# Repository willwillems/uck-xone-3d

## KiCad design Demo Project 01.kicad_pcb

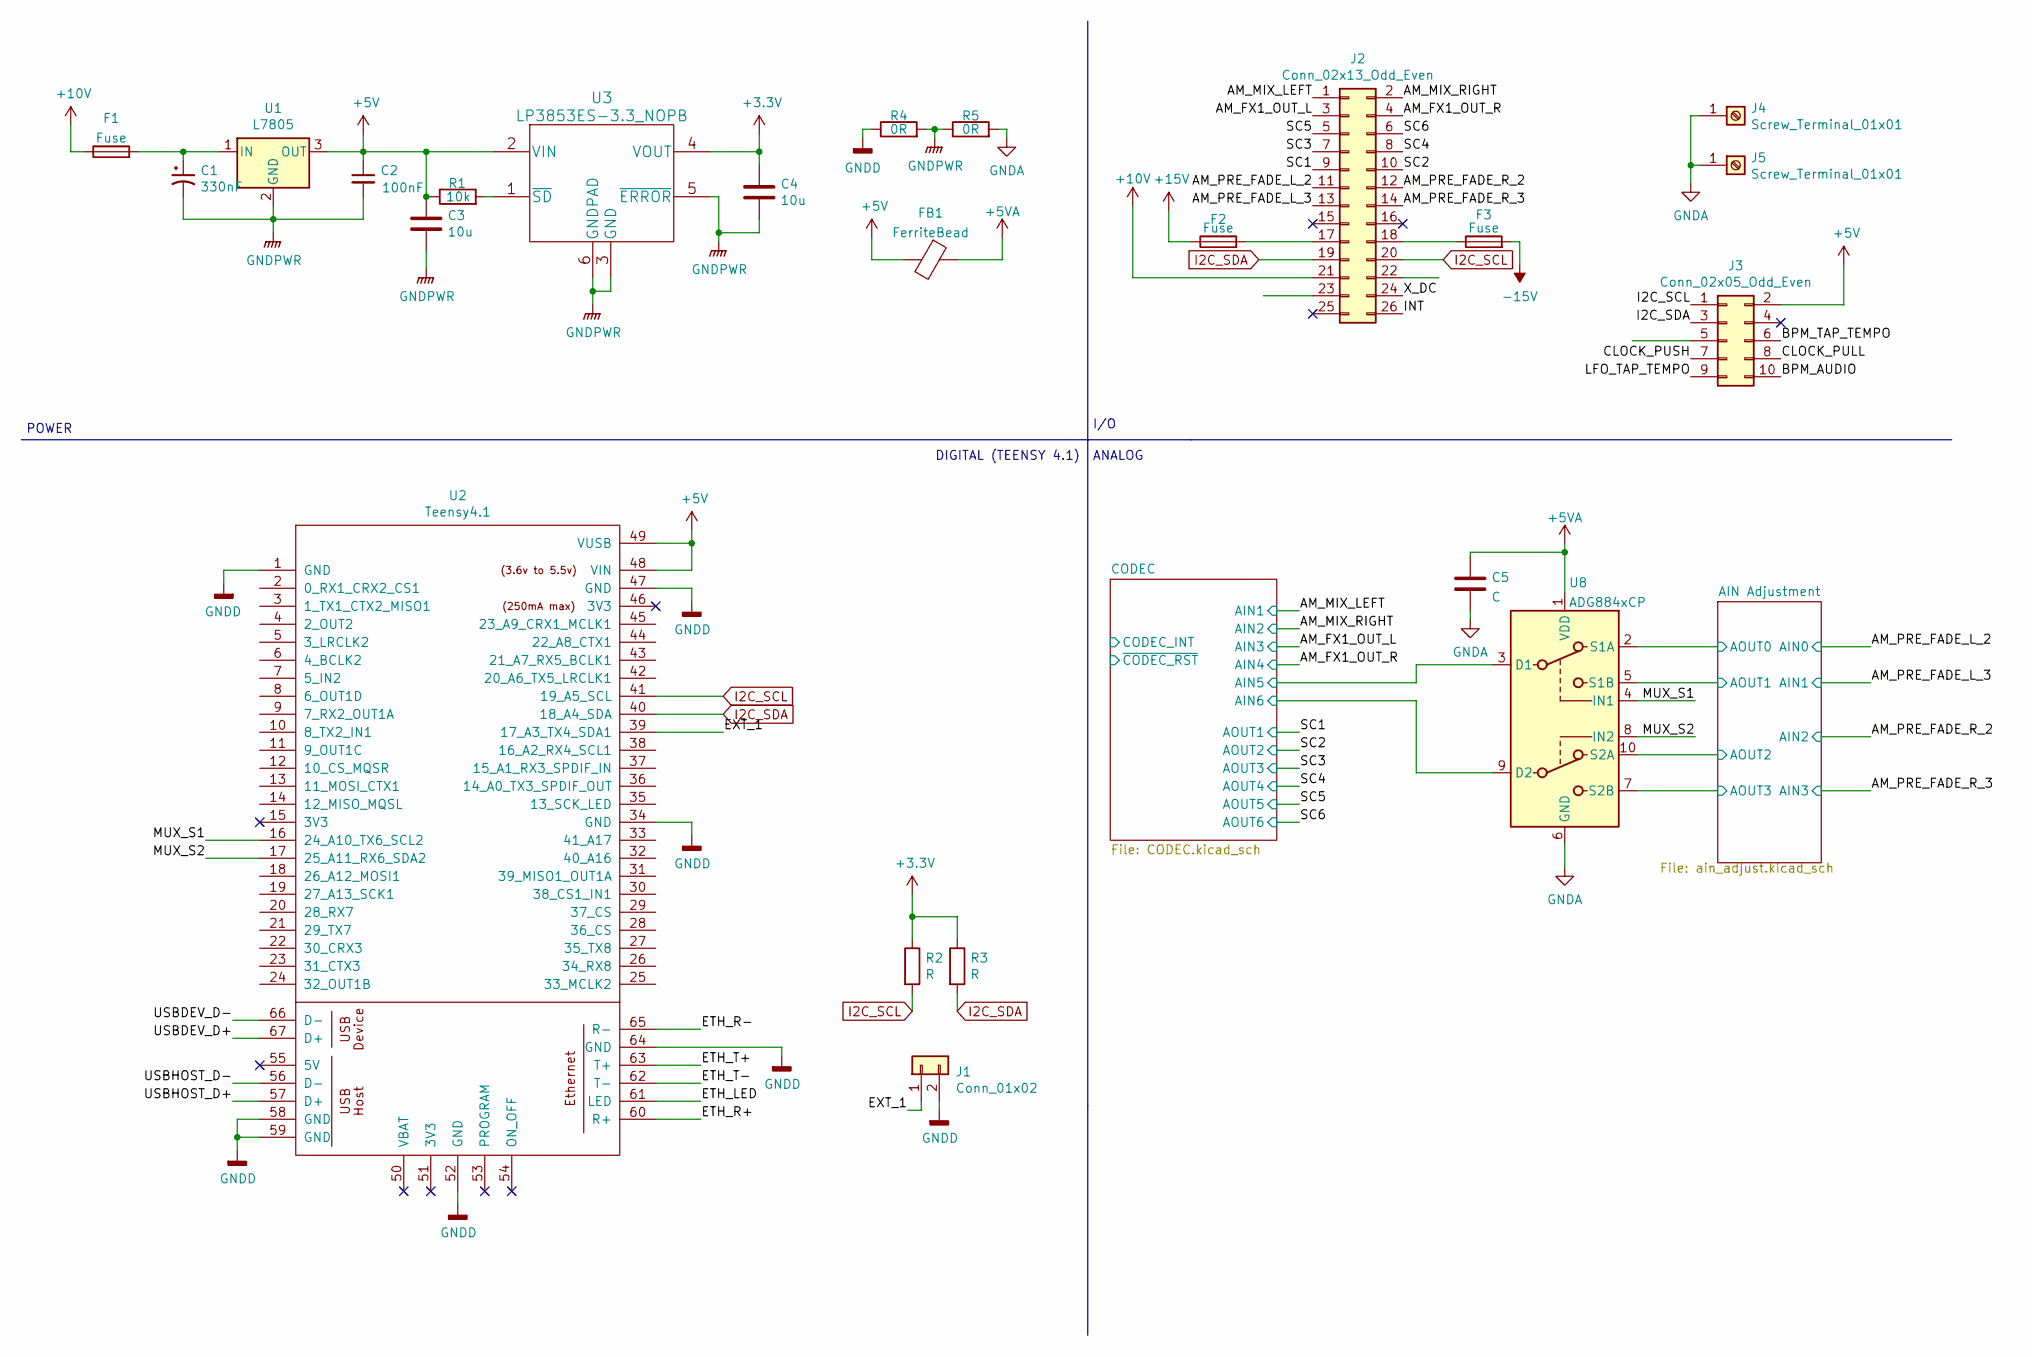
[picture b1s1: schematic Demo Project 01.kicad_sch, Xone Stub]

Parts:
C1: 330nF; CP_Radial_D10.0mm_P5.00mm
C2: 100nF; C_0603_1608Metric
C3, C4: 10u; C_0603_1608Metric_Pad1.08x0.95mm_HandSolder
C5: C; C_0603_1608Metric_Pad1.08x0.95mm_HandSolder
F1, F2, F3: Fuse; Fuse_0805_2012Metric
FB1: FerriteBead; C_0805_2012Metric_Pad1.18x1.45mm_HandSolder
J1: Conn_01x02; PinHeader_1x02_P2.54mm_Vertical
J2: Conn_02x13_Odd_Even; PinHeader_2x13_P2.54mm_Vertical
J3: Conn_02x05_Odd_Even; IDC-Header_2x05_P2.54mm_Horizontal
J4, J5: Screw_Terminal_01x01; MountingHole_3.2mm_M3_Pad_Via
R1: 10k; R_0603_1608Metric_Pad0.98x0.95mm_HandSolder
R2, R3: R; R_0603_1608Metric_Pad0.98x0.95mm_HandSolder
R4, R5: 0R; R_0603_1608Metric_Pad0.98x0.95mm_HandSolder
U1: L7805; TO-263-2
U2: Teensy4.1; Teensy41
U3: LP3853ES-3.3_NOPB; TO-263-5_TabPin6
U8: ADG884xCP; LFCSP-WD-10-1EP_3x3mm_P0.5mm_EP1.64x2.38mm

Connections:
+3V3: C4.1, R2.1, R3.1, U3.4 (VOUT); also elsewhere on the board
+5V: C2.1, C3.1, FB1.2, J3.2, R1.1, U1.3 (OUT), U2.48 (VIN), U2.49 (VUSB), U3.2 (VIN)
+5VA: C5.1, FB1.1, U8.1 (VDD); also elsewhere on the board
+10V: F1.1, J2.21
+15V: F2.1; also elsewhere on the board
-15V: F3.2; also elsewhere on the board
/AIN Adjustment/AOUT0: U8.2 (S1A); also elsewhere on the board
/AIN Adjustment/AOUT1: U8.5 (S1B); also elsewhere on the board
/AIN Adjustment/AOUT2: U8.10 (S2A); also elsewhere on the board
/AIN Adjustment/AOUT3: U8.7 (S2B); also elsewhere on the board
/AM_FX1_OUT_L: J2.3; also elsewhere on the board
/AM_FX1_OUT_R: J2.4; also elsewhere on the board
/AM_MIX_LEFT: J2.1; also elsewhere on the board
/AM_MIX_RIGHT: J2.2; also elsewhere on the board
/AM_PRE_FADE_L_2: J2.11; also elsewhere on the board
/AM_PRE_FADE_L_3: J2.13; also elsewhere on the board
/AM_PRE_FADE_R_2: J2.12; also elsewhere on the board
/AM_PRE_FADE_R_3: J2.14; also elsewhere on the board
/BPM_AUDIO: J3.10
/BPM_TAP_TEMPO: J3.6
/CLOCK_PULL: J3.8
/CLOCK_PUSH: J3.7
/CODEC/AIN5: U8.3 (D1); also elsewhere on the board
/CODEC/AIN6: U8.9 (D2); also elsewhere on the board
/ETH_LED: U2.61 (LED)
/ETH_R+: U2.60 (R+)
/ETH_R-: U2.65 (R-)
/ETH_T+: U2.63 (T+)
/ETH_T-: U2.62 (T-)
/EXT_1: J1.1, U2.39 (17_A3_TX4_SDA1)
/INT: J2.26
/LFO_TAP_TEMPO: J3.9
/MUX_S1: U2.16 (24_A10_TX6_SCL2), U8.4 (IN1)
/MUX_S2: U2.17 (25_A11_RX6_SDA2), U8.8 (IN2)
/SC1: J2.9; also elsewhere on the board
/SC2: J2.10; also elsewhere on the board
/SC3: J2.7; also elsewhere on the board
/SC4: J2.8; also elsewhere on the board
/SC5: J2.5; also elsewhere on the board
/SC6: J2.6; also elsewhere on the board
/USBDEV_D+: U2.67 (D+)
/USBDEV_D-: U2.66 (D-)
/USBHOST_D+: U2.57 (D+)
/USBHOST_D-: U2.56 (D-)
/X_DC: J2.24
GNDA: C5.2, J4.1, J5.1, R5.2, U8.6 (GND), U8.11 (GND); also elsewhere on the board
GNDD: J1.2, R4.1, U2.1 (GND), U2.34 (GND), U2.47 (GND), U2.52 (GND), U2.58 (GND), U2.59 (GND), U2.64 (GND); also elsewhere on the board
GNDPWR: C1.2, C2.2, C3.2, C4.2, R4.2, R5.1, U1.2 (GND), U3.3 (GND), U3.5 (~ERROR), U3.6 (GNDPAD)
I2C_SCL: J2.20, J3.1, R2.2, U2.41 (19_A5_SCL); also elsewhere on the board
I2C_SDA: J2.19, J3.3, R3.2, U2.40 (18_A4_SDA); also elsewhere on the board
unnamed: C1.1, F1.2, U1.1 (IN)
unnamed: F2.2, J2.17
unnamed: F3.1, J2.18
unnamed: R1.2, U3.1 (~SD)

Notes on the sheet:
I/O
ANALOG
DIGITAL (TEENSY 4.1)
POWER

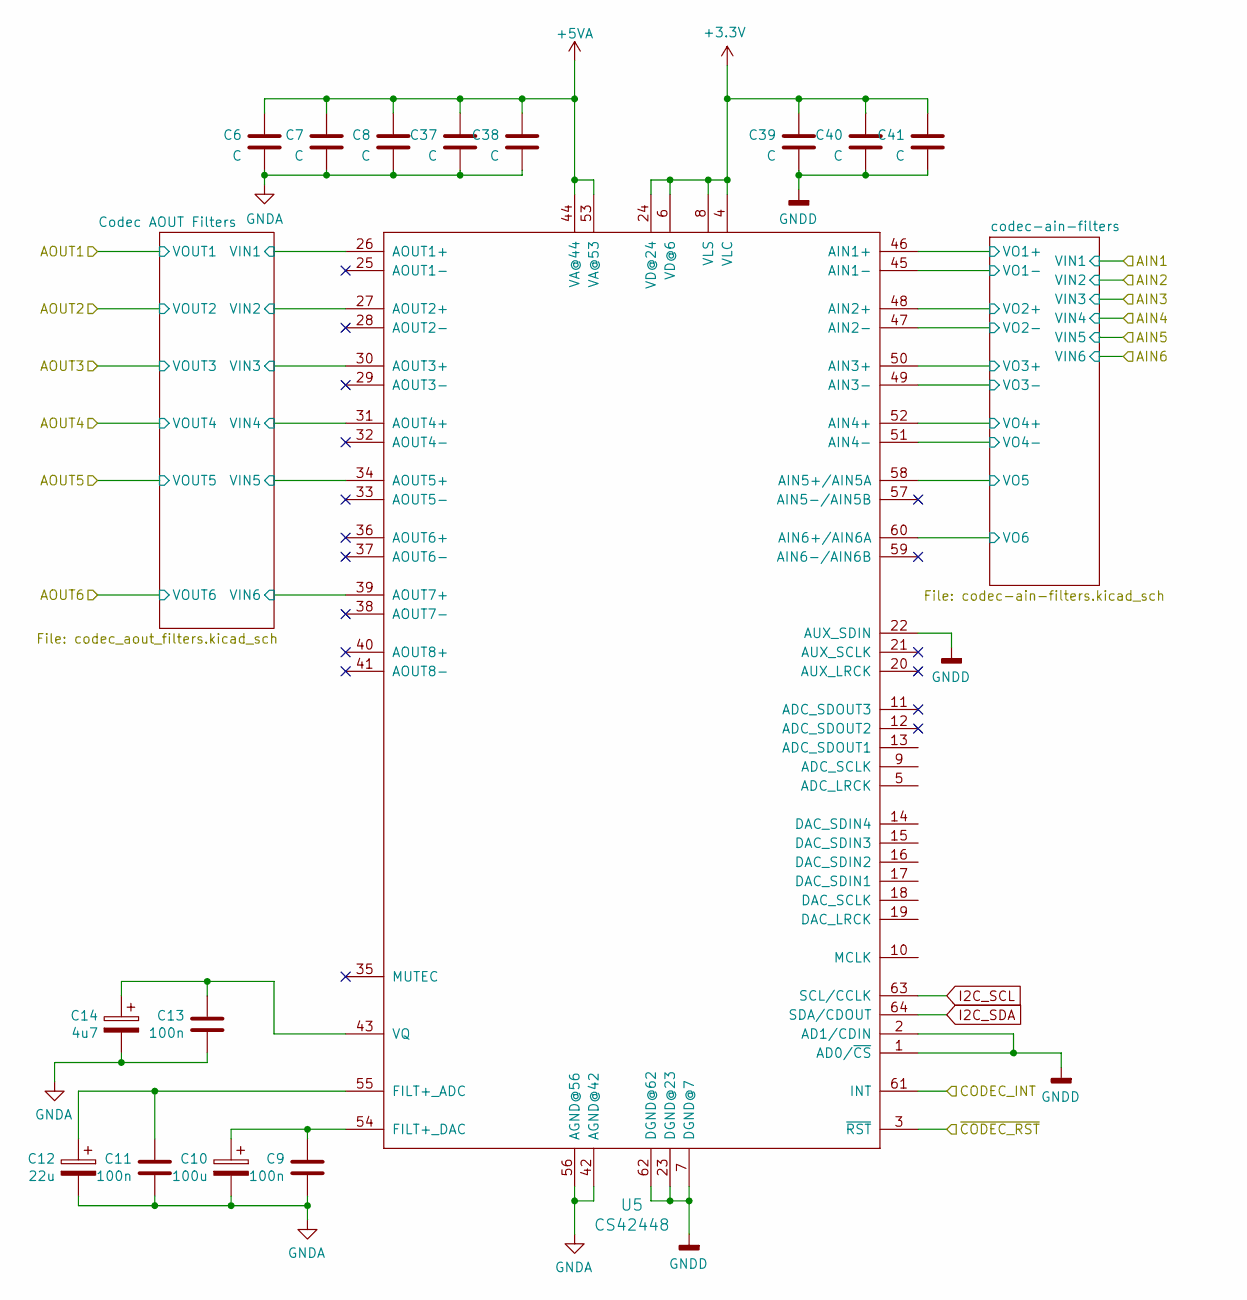
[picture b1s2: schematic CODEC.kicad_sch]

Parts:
C6, C7, C8, C37, C38, C39, C40, C41: C; C_0603_1608Metric_Pad1.08x0.95mm_HandSolder
C9, C11, C13: 100n; C_0603_1608Metric_Pad1.08x0.95mm_HandSolder
C10: 100u; C_0603_1608Metric_Pad1.08x0.95mm_HandSolder
C12: 22u; C_0603_1608Metric_Pad1.08x0.95mm_HandSolder
C14: 4u7; C_0603_1608Metric_Pad1.08x0.95mm_HandSolder
U5: CS42448; LQFP-64_10x10mm_P0.5mm

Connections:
+3V3: C39.1, C40.1, C41.1, U5.4 (VLC), U5.6 (VD@6), U5.8 (VLS), U5.24 (VD@24); also elsewhere on the board
+5VA: C6.1, C7.1, C8.1, C37.1, C38.1, U5.44 (VA@44), U5.53 (VA@53); also elsewhere on the board
/CODEC/CODEC_INT: U5.61 (INT)
/CODEC/Codec AOUT Filters/VIN1: U5.26 (AOUT1+); also elsewhere on the board
/CODEC/Codec AOUT Filters/VIN2: U5.27 (AOUT2+); also elsewhere on the board
/CODEC/Codec AOUT Filters/VIN3: U5.30 (AOUT3+); also elsewhere on the board
/CODEC/Codec AOUT Filters/VIN4: U5.31 (AOUT4+); also elsewhere on the board
/CODEC/Codec AOUT Filters/VIN5: U5.34 (AOUT5+); also elsewhere on the board
/CODEC/Codec AOUT Filters/VIN6: U5.39 (AOUT7+); also elsewhere on the board
/CODEC/codec-ain-filters/VO1+: U5.46 (AIN1+); also elsewhere on the board
/CODEC/codec-ain-filters/VO1-: U5.45 (AIN1-); also elsewhere on the board
/CODEC/codec-ain-filters/VO2+: U5.48 (AIN2+); also elsewhere on the board
/CODEC/codec-ain-filters/VO2-: U5.47 (AIN2-); also elsewhere on the board
/CODEC/codec-ain-filters/VO3+: U5.50 (AIN3+); also elsewhere on the board
/CODEC/codec-ain-filters/VO3-: U5.49 (AIN3-); also elsewhere on the board
/CODEC/codec-ain-filters/VO4+: U5.52 (AIN4+); also elsewhere on the board
/CODEC/codec-ain-filters/VO4-: U5.51 (AIN4-); also elsewhere on the board
/CODEC/codec-ain-filters/VO5: U5.58 (AIN5+/AIN5A); also elsewhere on the board
/CODEC/codec-ain-filters/VO6: U5.60 (AIN6+/AIN6A); also elsewhere on the board
/CODEC/~CODEC_RST: U5.3 (~RST)
GNDA: C6.2, C7.2, C8.2, C9.2, C10.2, C11.2, C12.2, C13.2, C14.2, C37.2, C38.2, U5.42 (AGND@42), U5.56 (AGND@56); also elsewhere on the board
GNDD: C39.2, C40.2, C41.2, U5.1 (AD0/~CS), U5.2 (AD1/CDIN), U5.7 (DGND@7), U5.22 (AUX_SDIN), U5.23 (DGND@23), U5.62 (DGND@62); also elsewhere on the board
I2C_SCL: U5.63 (SCL/CCLK); also elsewhere on the board
I2C_SDA: U5.64 (SDA/CDOUT); also elsewhere on the board
unnamed: C9.1, C10.1, U5.54 (FILT+_DAC)
unnamed: C11.1, C12.1, U5.55 (FILT+_ADC)
unnamed: C13.1, C14.1, U5.43 (VQ)

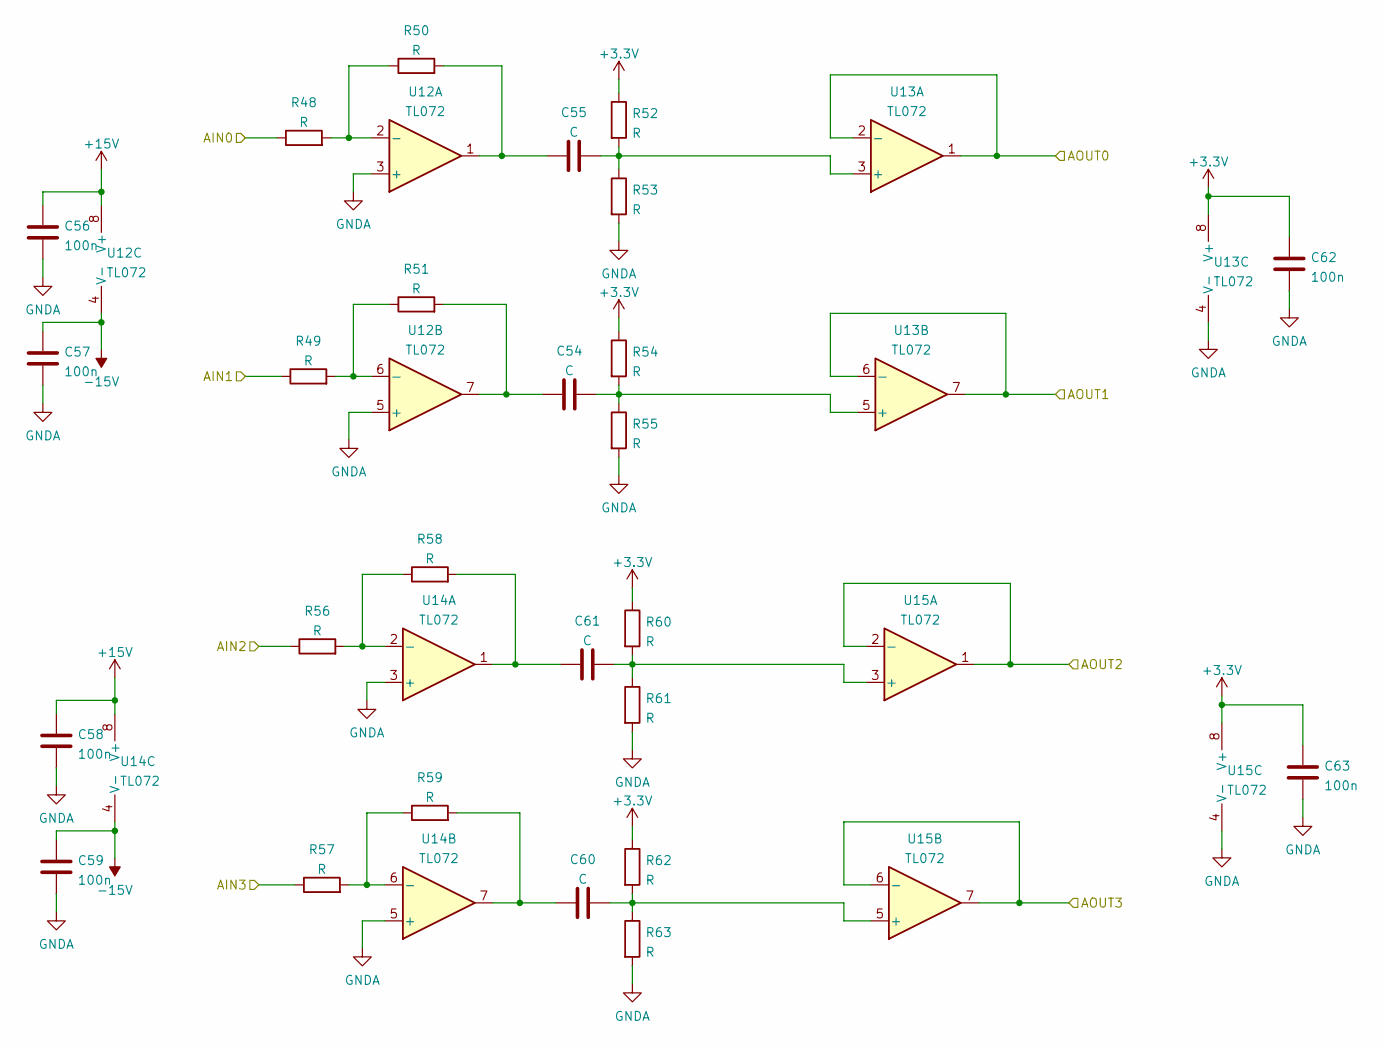
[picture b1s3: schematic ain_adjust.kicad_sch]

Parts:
C54, C55, C60, C61: C; C_0603_1608Metric_Pad1.08x0.95mm_HandSolder
C56, C57, C58, C59, C62, C63: 100n; C_0603_1608Metric_Pad1.08x0.95mm_HandSolder
R48, R49, R50, R51, R52, R53, R54, R55, R56, R57, R58, R59, R60, R61, R62, R63: R; R_0603_1608Metric_Pad0.98x0.95mm_HandSolder
U12, U13, U14, U15: TL072; SOIC-8_3.9x4.9mm_P1.27mm

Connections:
+3V3: C62.1, C63.1, R52.1, R54.1, R60.1, R62.1, U13.8 (V+), U15.8 (V+); also elsewhere on the board
+15V: C56.1, C58.1, U12.8 (V+), U14.8 (V+); also elsewhere on the board
-15V: C57.1, C59.1, U12.4 (V-), U14.4 (V-); also elsewhere on the board
/AIN Adjustment/AOUT0: U13.1, U13.2 (-); also elsewhere on the board
/AIN Adjustment/AOUT1: U13.6 (-), U13.7; also elsewhere on the board
/AIN Adjustment/AOUT2: U15.1, U15.2 (-); also elsewhere on the board
/AIN Adjustment/AOUT3: U15.6 (-), U15.7; also elsewhere on the board
/AM_PRE_FADE_L_2: R48.1; also elsewhere on the board
/AM_PRE_FADE_L_3: R49.1; also elsewhere on the board
/AM_PRE_FADE_R_2: R56.1; also elsewhere on the board
/AM_PRE_FADE_R_3: R57.1; also elsewhere on the board
GNDA: C56.2, C57.2, C58.2, C59.2, C62.2, C63.2, R53.2, R55.2, R61.2, R63.2, U12.3 (+), U12.5 (+), U13.4 (V-), U14.3 (+), U14.5 (+), U15.4 (V-); also elsewhere on the board
unnamed: C54.1, R51.2, U12.7
unnamed: C54.2, R54.2, R55.1, U13.5 (+)
unnamed: C55.1, R50.2, U12.1
unnamed: C55.2, R52.2, R53.1, U13.3 (+)
unnamed: C60.1, R59.2, U14.7
unnamed: C60.2, R62.2, R63.1, U15.5 (+)
unnamed: C61.1, R58.2, U14.1
unnamed: C61.2, R60.2, R61.1, U15.3 (+)
unnamed: R48.2, R50.1, U12.2 (-)
unnamed: R49.2, R51.1, U12.6 (-)
unnamed: R56.2, R58.1, U14.2 (-)
unnamed: R57.2, R59.1, U14.6 (-)

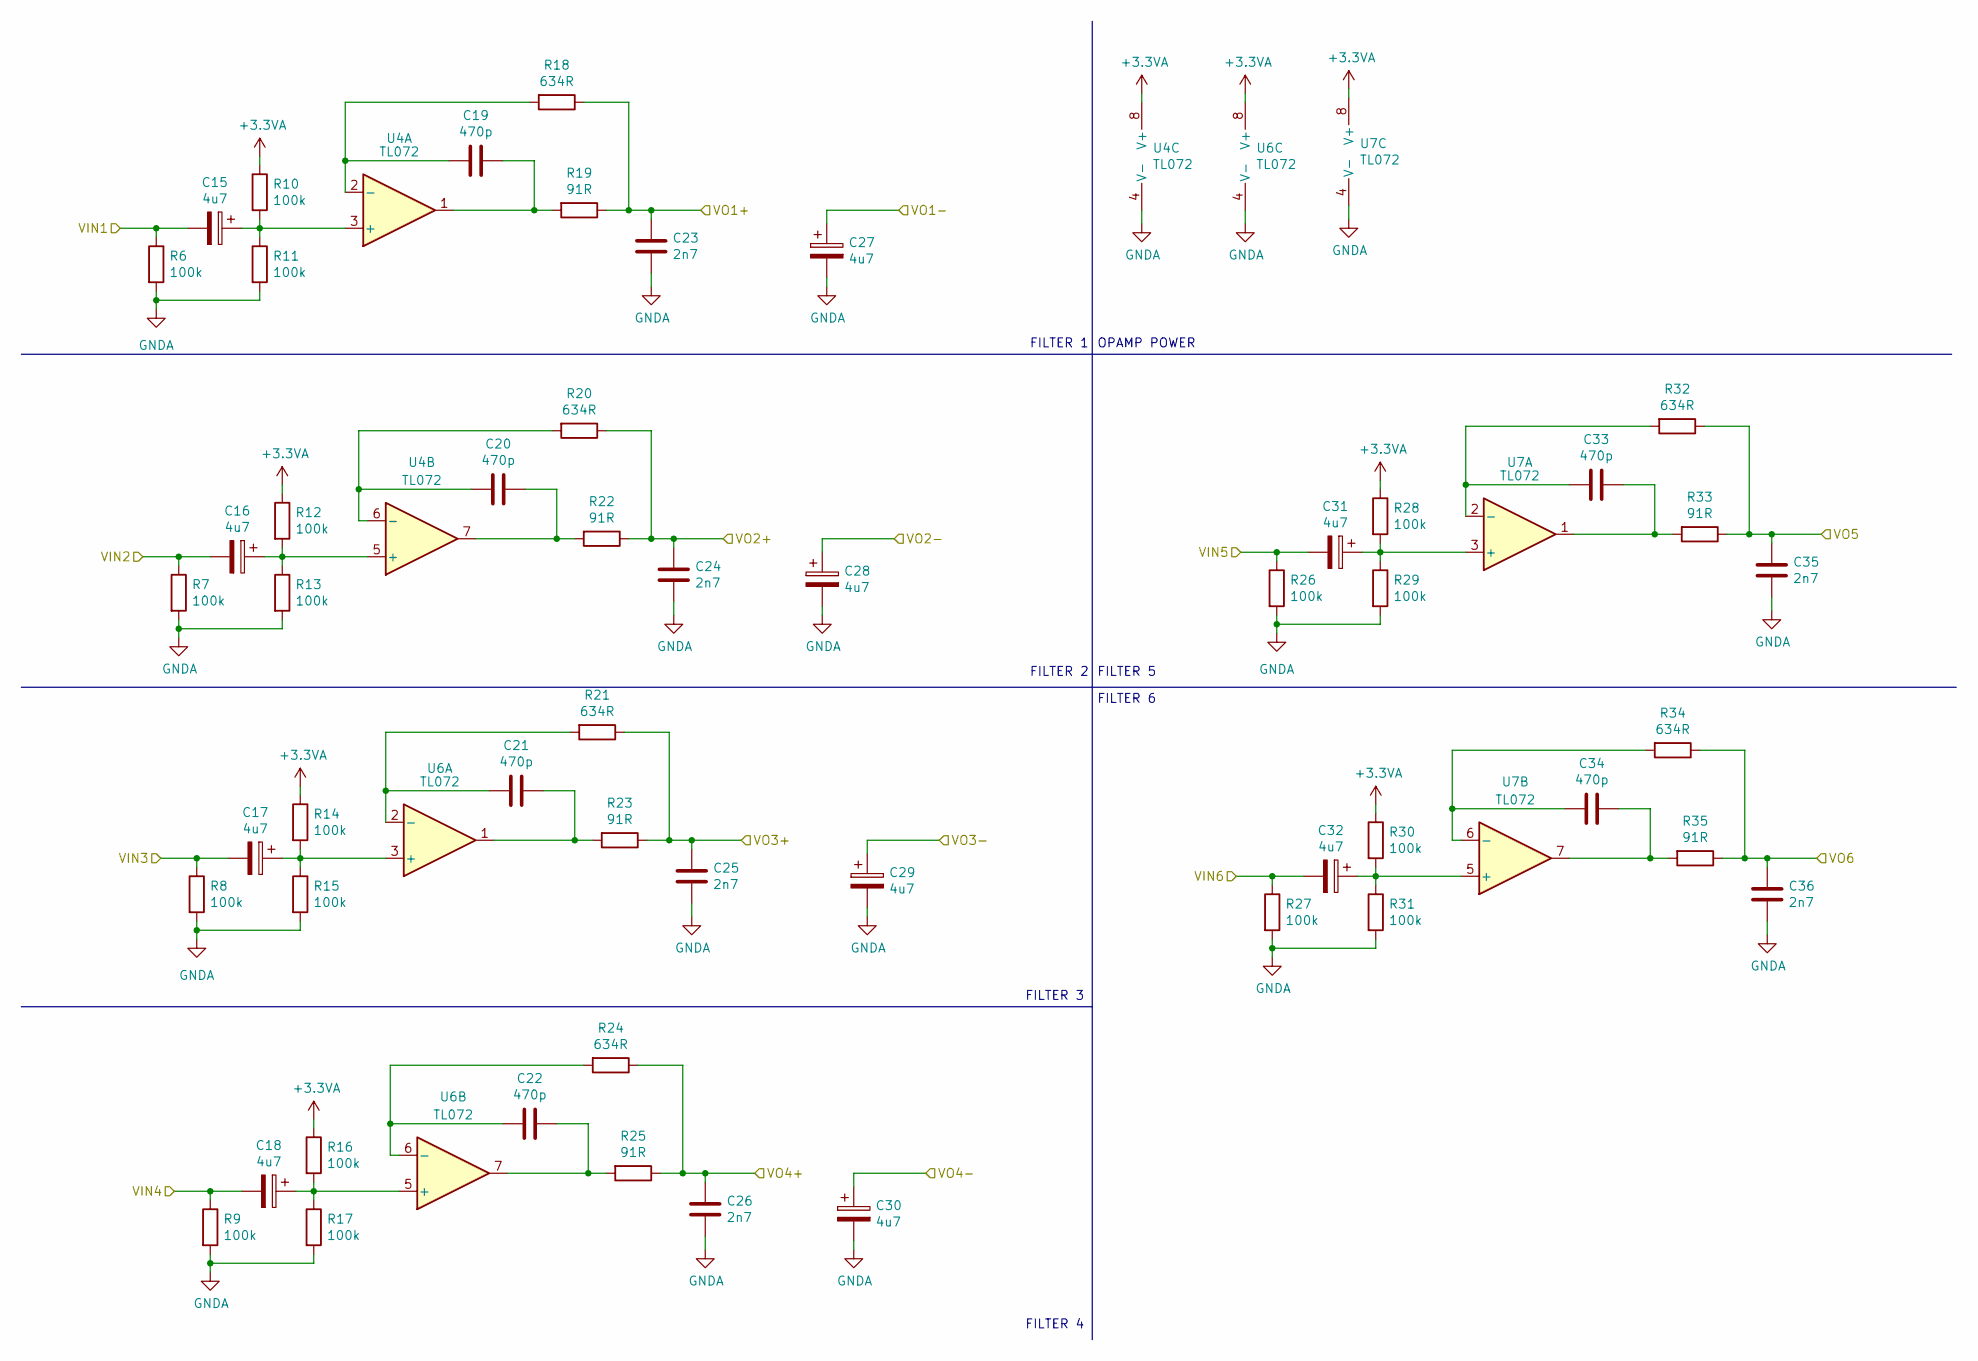
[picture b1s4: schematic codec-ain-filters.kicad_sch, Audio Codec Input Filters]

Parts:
C15, C16, C17, C18, C27, C28, C29, C30, C31, C32: 4u7; C_0603_1608Metric_Pad1.08x0.95mm_HandSolder
C19, C20, C21, C22, C33, C34: 470p; C_0603_1608Metric_Pad1.08x0.95mm_HandSolder
C23, C24, C25, C26, C35, C36: 2n7; C_0603_1608Metric_Pad1.08x0.95mm_HandSolder
R6, R7, R8, R9, R10, R11, R12, R13, R14, R15, R16, R17, R26, R27, R28, R29, R30, R31: 100k; R_0603_1608Metric_Pad0.98x0.95mm_HandSolder
R18, R20, R21, R24, R32, R34: 634R; R_0603_1608Metric_Pad0.98x0.95mm_HandSolder
R19, R22, R23, R25, R33, R35: 91R; R_0603_1608Metric_Pad0.98x0.95mm_HandSolder
U4, U6, U7: TL072; SOIC-8_3.9x4.9mm_P1.27mm

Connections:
+3.3VA: R10.1, R12.1, R14.1, R16.1, R28.1, R30.1, U4.8 (V+), U6.8 (V+), U7.8 (V+)
/AM_FX1_OUT_L: C17.2, R8.1; also elsewhere on the board
/AM_FX1_OUT_R: C18.2, R9.1; also elsewhere on the board
/AM_MIX_LEFT: C15.2, R6.1; also elsewhere on the board
/AM_MIX_RIGHT: C16.2, R7.1; also elsewhere on the board
/CODEC/AIN5: C31.2, R26.1; also elsewhere on the board
/CODEC/AIN6: C32.2, R27.1; also elsewhere on the board
/CODEC/codec-ain-filters/VO1+: C23.1, R18.1, R19.1; also elsewhere on the board
/CODEC/codec-ain-filters/VO1-: C27.1; also elsewhere on the board
/CODEC/codec-ain-filters/VO2+: C24.1, R20.1, R22.1; also elsewhere on the board
/CODEC/codec-ain-filters/VO2-: C28.1; also elsewhere on the board
/CODEC/codec-ain-filters/VO3+: C25.1, R21.1, R23.1; also elsewhere on the board
/CODEC/codec-ain-filters/VO3-: C29.1; also elsewhere on the board
/CODEC/codec-ain-filters/VO4+: C26.1, R24.1, R25.1; also elsewhere on the board
/CODEC/codec-ain-filters/VO4-: C30.1; also elsewhere on the board
/CODEC/codec-ain-filters/VO5: C35.1, R32.1, R33.1; also elsewhere on the board
/CODEC/codec-ain-filters/VO6: C36.1, R34.1, R35.1; also elsewhere on the board
GNDA: C23.2, C24.2, C25.2, C26.2, C27.2, C28.2, C29.2, C30.2, C35.2, C36.2, R6.2, R7.2, R8.2, R9.2, R11.2, R13.2, R15.2, R17.2, R26.2, R27.2, R29.2, R31.2, U4.4 (V-), U6.4 (V-), U7.4 (V-); also elsewhere on the board
unnamed: C15.1, R10.2, R11.1, U4.3 (+)
unnamed: C16.1, R12.2, R13.1, U4.5 (+)
unnamed: C17.1, R14.2, R15.1, U6.3 (+)
unnamed: C18.1, R16.2, R17.1, U6.5 (+)
unnamed: C19.1, R19.2, U4.1
unnamed: C19.2, R18.2, U4.2 (-)
unnamed: C20.1, R22.2, U4.7
unnamed: C20.2, R20.2, U4.6 (-)
unnamed: C21.1, R23.2, U6.1
unnamed: C21.2, R21.2, U6.2 (-)
unnamed: C22.1, R25.2, U6.7
unnamed: C22.2, R24.2, U6.6 (-)
unnamed: C31.1, R28.2, R29.1, U7.3 (+)
unnamed: C32.1, R30.2, R31.1, U7.5 (+)
unnamed: C33.1, R33.2, U7.1
unnamed: C33.2, R32.2, U7.2 (-)
unnamed: C34.1, R35.2, U7.7
unnamed: C34.2, R34.2, U7.6 (-)

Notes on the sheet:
FILTER 3
FILTER 2
FILTER 6
FILTER 5
OPAMP POWER
FILTER 1
FILTER 4

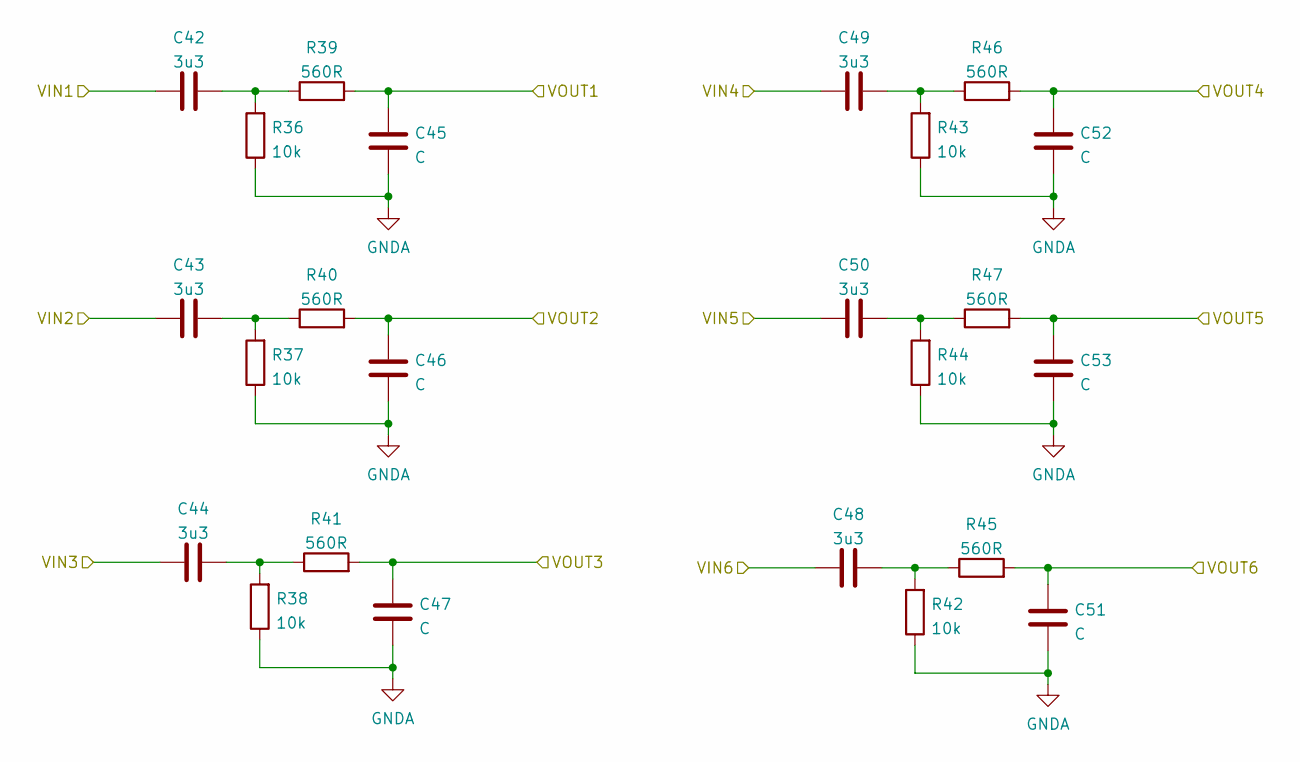
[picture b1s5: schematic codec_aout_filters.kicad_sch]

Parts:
C42, C43, C44, C48, C49, C50: 3u3; C_0603_1608Metric_Pad1.08x0.95mm_HandSolder
C45, C46, C47, C51, C52, C53: C; C_0603_1608Metric_Pad1.08x0.95mm_HandSolder
R36, R37, R38, R42, R43, R44: 10k; R_0603_1608Metric_Pad0.98x0.95mm_HandSolder
R39, R40, R41, R45, R46, R47: 560R; R_0603_1608Metric_Pad0.98x0.95mm_HandSolder

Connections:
/CODEC/Codec AOUT Filters/VIN1: C42.1; also elsewhere on the board
/CODEC/Codec AOUT Filters/VIN2: C43.1; also elsewhere on the board
/CODEC/Codec AOUT Filters/VIN3: C44.1; also elsewhere on the board
/CODEC/Codec AOUT Filters/VIN4: C49.1; also elsewhere on the board
/CODEC/Codec AOUT Filters/VIN5: C50.1; also elsewhere on the board
/CODEC/Codec AOUT Filters/VIN6: C48.1; also elsewhere on the board
/SC1: C45.2, R39.2; also elsewhere on the board
/SC2: C46.2, R40.2; also elsewhere on the board
/SC3: C47.2, R41.2; also elsewhere on the board
/SC4: C52.2, R46.2; also elsewhere on the board
/SC5: C53.2, R47.2; also elsewhere on the board
/SC6: C51.2, R45.2; also elsewhere on the board
GNDA: C45.1, C46.1, C47.1, C51.1, C52.1, C53.1, R36.1, R37.1, R38.1, R42.1, R43.1, R44.1; also elsewhere on the board
unnamed: C42.2, R36.2, R39.1
unnamed: C43.2, R37.2, R40.1
unnamed: C44.2, R38.2, R41.1
unnamed: C48.2, R42.2, R45.1
unnamed: C49.2, R43.2, R46.1
unnamed: C50.2, R44.2, R47.1

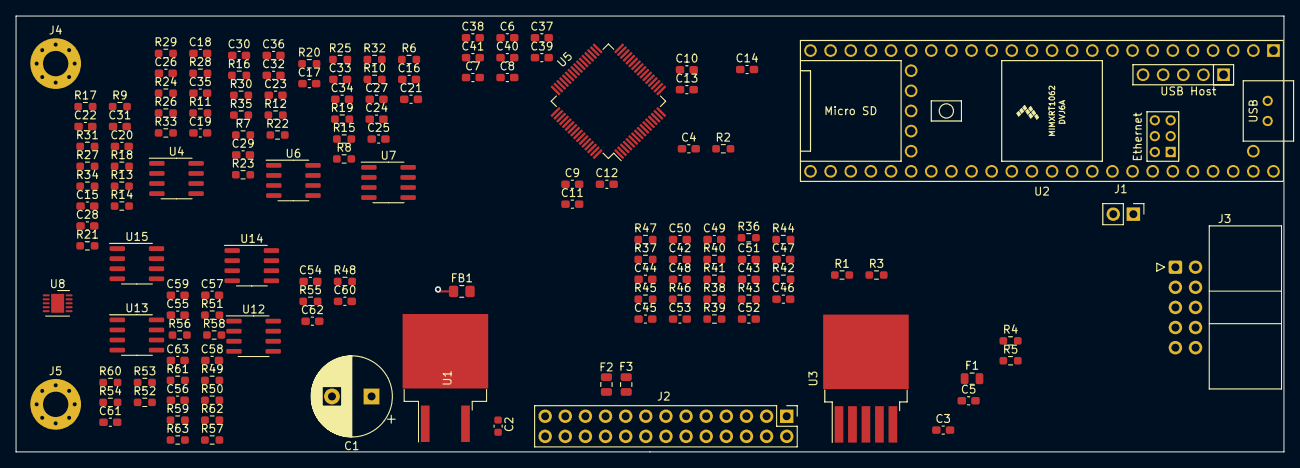
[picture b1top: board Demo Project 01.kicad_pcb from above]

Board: 4 copper layers, 160.0 x 55.0 mm, 147 parts (0 on the bottom side), 94 nets.

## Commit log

2021-12-22 init
2021-12-23 - Cleaned up schematic layout by creating dedicated sheet for codec as well as analog input filters in addition to the main Teensy sheet - Added schematics for all AIN filters based on codec datashee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
2022-01-27 Schematic 95% done, some digital connection and part value assignment remaining. Part placement/tentative planes done
